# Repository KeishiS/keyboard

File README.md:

# README

## Dependencies

- `https://github.com/foostan/kbd`
- `https://github.com/keebio/Keebio-Parts.pretty`

```
> ln -s ./keyboard/keyboards/keishis $HOME/qmk_firmware/keyboards/keishis
> qmk compile -kb keishis/ot_board -km default
> qmk flash keishis_ot_board_default.hex
```

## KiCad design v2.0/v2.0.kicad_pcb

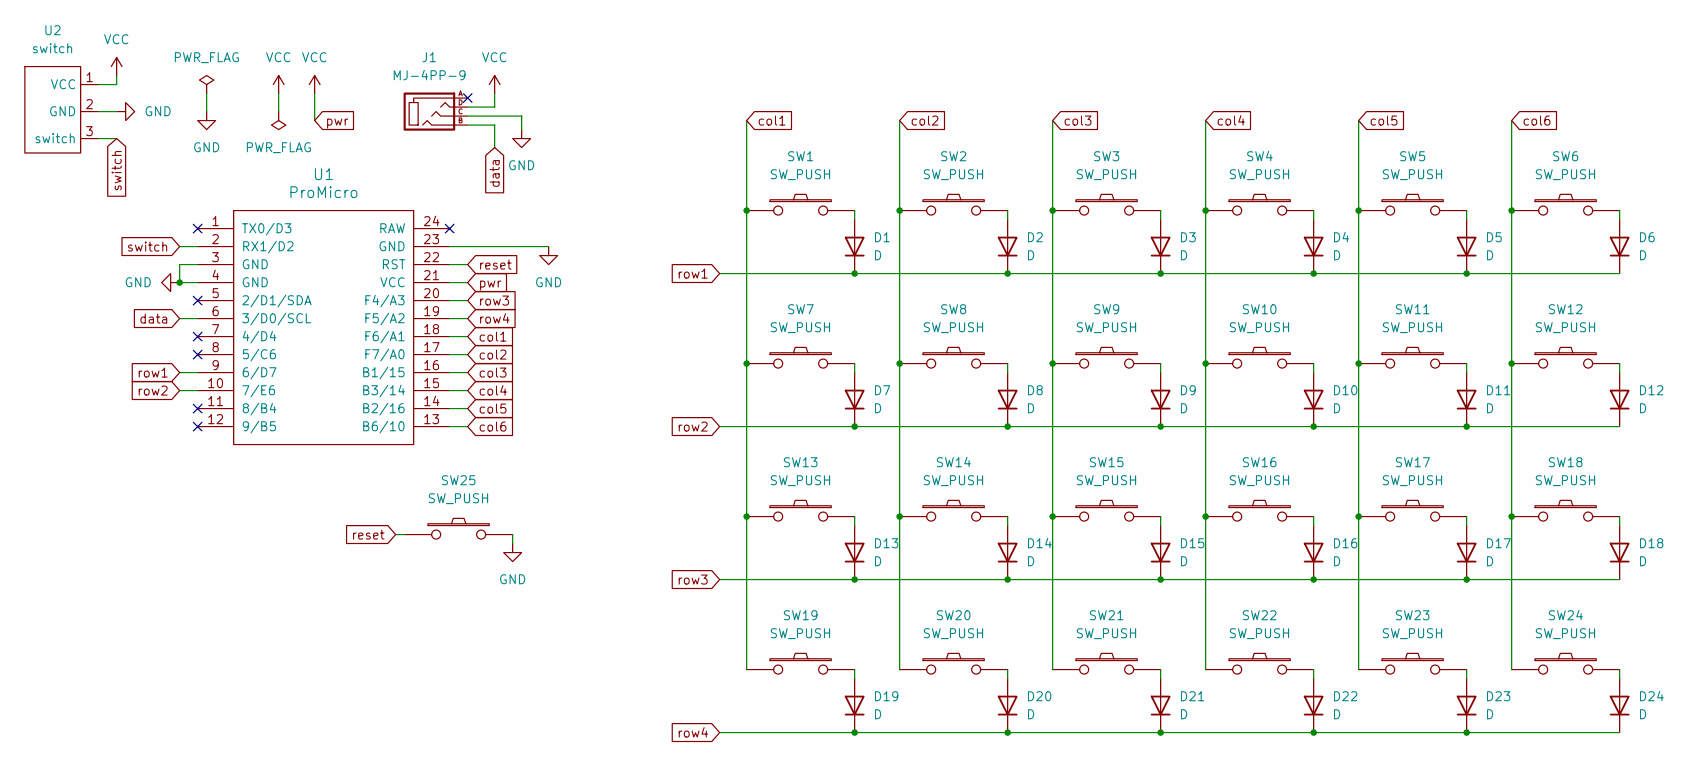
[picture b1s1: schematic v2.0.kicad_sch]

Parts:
D1, D2, D3, D4, D5, D6, D7, D8, D9, D10, D11, D12, D13, D14, D15, D16, D17, D18, D19, D20, D21, D22, D23, D24: D; Diode-dual
J1: MJ-4PP-9; MJ-4PP-9_reversible
SW1, SW2, SW3, SW4, SW5, SW6, SW7, SW8, SW9, SW10, SW11, SW12, SW13, SW14, SW15, SW16, SW17, SW18, SW19, SW20, SW21, SW22, SW23, SW24: SW_PUSH; choc1_0.8u_reversible
SW25: SW_PUSH; ResetSW
U1: ProMicro
U2: switch; triangle

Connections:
GND: J1.C, SW25.2, U1.3 (GND), U1.4 (GND), U1.23 (GND), U2.2 (GND)
unnamed: D1.2 (A), SW1.2
unnamed: D2.2 (A), SW2.2
unnamed: D3.2 (A), SW3.2
unnamed: D4.2 (A), SW4.2
unnamed: D5.2 (A), SW5.2
unnamed: D6.2 (A), SW6.2
unnamed: D7.2 (A), SW7.2
unnamed: D8.2 (A), SW8.2
unnamed: D9.2 (A), SW9.2
unnamed: D10.2 (A), SW10.2
unnamed: D11.2 (A), SW11.2
unnamed: D12.2 (A), SW12.2
unnamed: D13.2 (A), SW13.2
unnamed: D14.2 (A), SW14.2
unnamed: D15.2 (A), SW15.2
unnamed: D16.2 (A), SW16.2
unnamed: D17.2 (A), SW17.2
unnamed: D18.2 (A), SW18.2
unnamed: D19.2 (A), SW19.2
unnamed: D20.2 (A), SW20.2
unnamed: D21.2 (A), SW21.2
unnamed: D22.2 (A), SW22.2
unnamed: D23.2 (A), SW23.2
unnamed: D24.2 (A), SW24.2
col1: SW1.1, SW7.1, SW13.1, SW19.1, U1.18 (F6/A1)
col2: SW2.1, SW8.1, SW14.1, SW20.1, U1.17 (F7/A0)
col3: SW3.1, SW9.1, SW15.1, SW21.1, U1.16 (B1/15)
col4: SW4.1, SW10.1, SW16.1, SW22.1, U1.15 (B3/14)
col5: SW5.1, SW11.1, SW17.1, SW23.1, U1.14 (B2/16)
col6: SW6.1, SW12.1, SW18.1, SW24.1, U1.13 (B6/10)
data: J1.B, U1.6 (3/D0/SCL)
pwr: J1.D, U1.21 (VCC), U2.1 (VCC)
reset: SW25.1, U1.22 (RST)
row1: D1.1 (K), D2.1 (K), D3.1 (K), D4.1 (K), D5.1 (K), D6.1 (K), U1.9 (6/D7)
row2: D7.1 (K), D8.1 (K), D9.1 (K), D10.1 (K), D11.1 (K), D12.1 (K), U1.10 (7/E6)
row3: D13.1 (K), D14.1 (K), D15.1 (K), D16.1 (K), D17.1 (K), D18.1 (K), U1.20 (F4/A3)
row4: D19.1 (K), D20.1 (K), D21.1 (K), D22.1 (K), D23.1 (K), D24.1 (K), U1.19 (F5/A2)
switch: U1.2 (RX1/D2), U2.3 (switch)

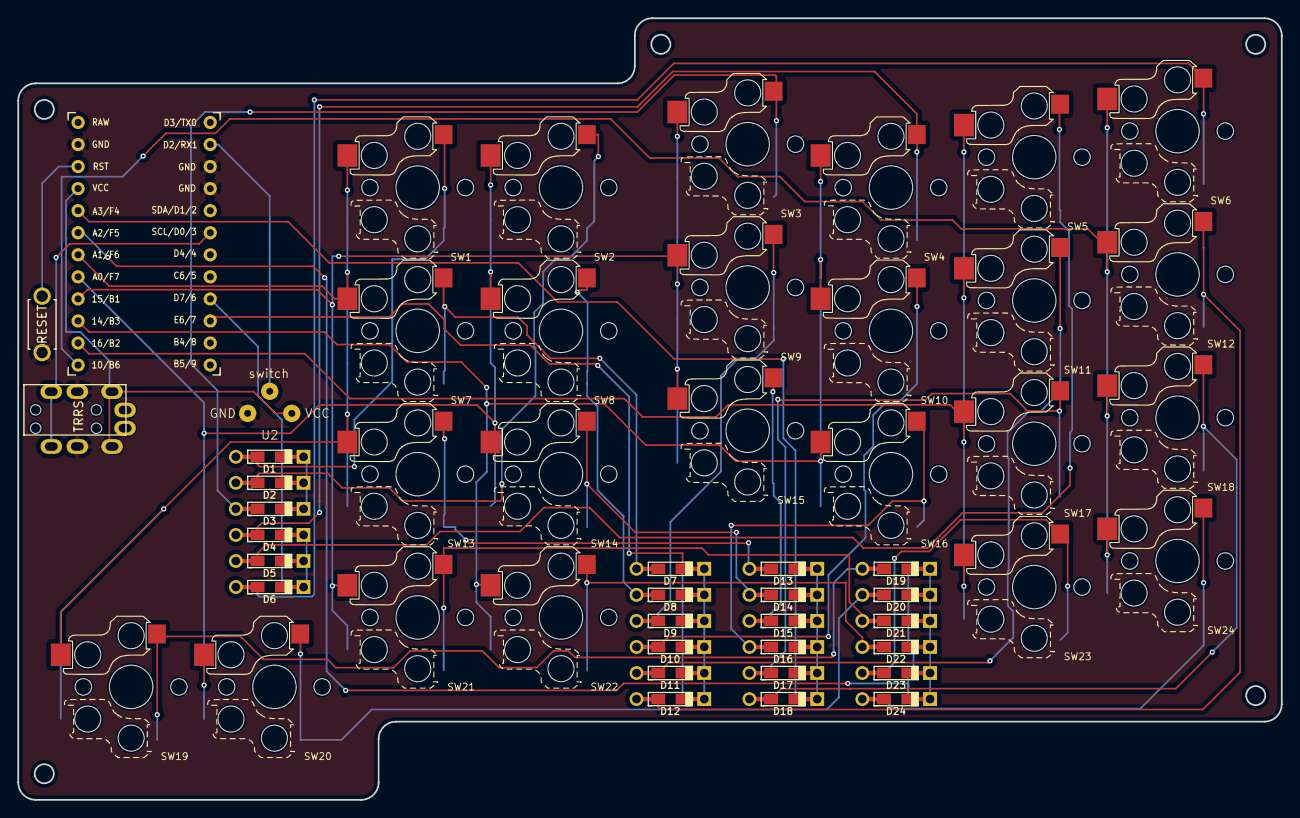
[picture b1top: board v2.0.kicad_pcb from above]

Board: 2 copper layers, 145.5 x 90.0 mm, 52 parts (0 on the bottom side), 39 nets.

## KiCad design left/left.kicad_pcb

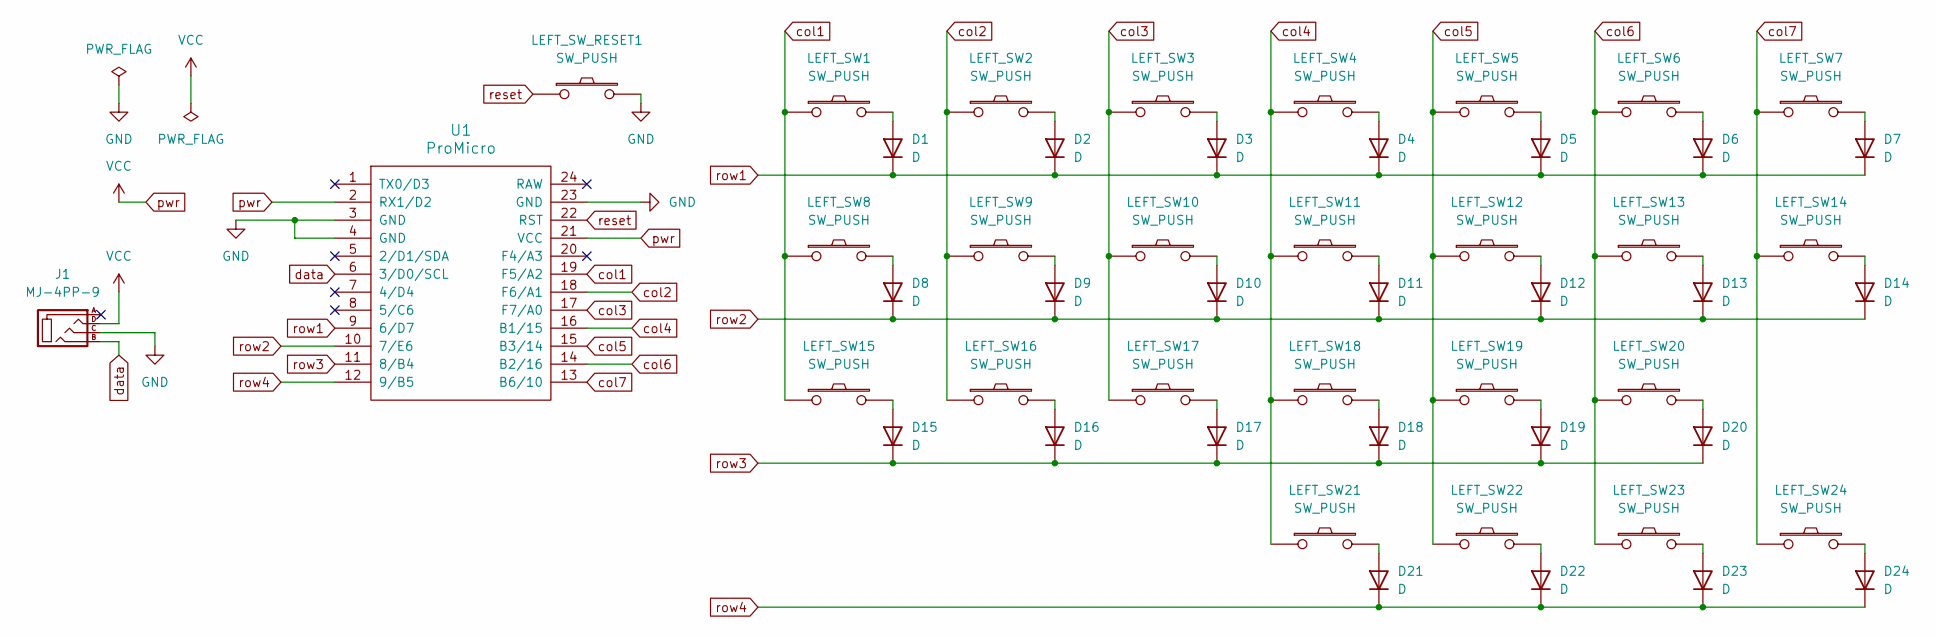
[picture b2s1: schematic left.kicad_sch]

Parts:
D1, D2, D3, D4, D5, D6, D7, D8, D9, D10, D11, D12, D13, D14, D15, D16, D17, D18, D19, D20, D21, D22, D23, D24: D; D3_TH_SMD
J1: MJ-4PP-9
LEFT_SW1, LEFT_SW2, LEFT_SW3, LEFT_SW4, LEFT_SW5, LEFT_SW6, LEFT_SW7, LEFT_SW8, LEFT_SW9, LEFT_SW10, LEFT_SW11, LEFT_SW12, LEFT_SW13, LEFT_SW14, LEFT_SW16, LEFT_SW17, LEFT_SW18, LEFT_SW19, LEFT_SW20, LEFT_SW21, LEFT_SW22, LEFT_SW23, LEFT_SW24: SW_PUSH; CherryMX_Choc_Hotswap
LEFT_SW15: SW_PUSH; CherryMX_Choc_Hotswap_1.5u
LEFT_SW_RESET1: SW_PUSH; ResetSW
U1: ProMicro; ProMicro_v2

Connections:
GND: J1.C, LEFT_SW_RESET1.2, U1.3 (GND), U1.4 (GND), U1.23 (GND)
unnamed: D1.2 (A), LEFT_SW1.2
unnamed: D2.2 (A), LEFT_SW2.2
unnamed: D3.2 (A), LEFT_SW3.2
unnamed: D4.2 (A), LEFT_SW4.2
unnamed: D5.2 (A), LEFT_SW5.2
unnamed: D6.2 (A), LEFT_SW6.2
unnamed: D7.2 (A), LEFT_SW7.2
unnamed: D8.2 (A), LEFT_SW8.2
unnamed: D9.2 (A), LEFT_SW9.2
unnamed: D10.2 (A), LEFT_SW10.2
unnamed: D11.2 (A), LEFT_SW11.2
unnamed: D12.2 (A), LEFT_SW12.2
unnamed: D13.2 (A), LEFT_SW13.2
unnamed: D14.2 (A), LEFT_SW14.2
unnamed: D15.2 (A), LEFT_SW15.2
unnamed: D16.2 (A), LEFT_SW16.2
unnamed: D17.2 (A), LEFT_SW17.2
unnamed: D18.2 (A), LEFT_SW18.2
unnamed: D19.2 (A), LEFT_SW19.2
unnamed: D20.2 (A), LEFT_SW20.2
unnamed: D21.2 (A), LEFT_SW21.2
unnamed: D22.2 (A), LEFT_SW22.2
unnamed: D23.2 (A), LEFT_SW23.2
unnamed: D24.2 (A), LEFT_SW24.2
col1: LEFT_SW1.1, LEFT_SW8.1, LEFT_SW15.1, U1.19 (F5/A2)
col2: LEFT_SW2.1, LEFT_SW9.1, LEFT_SW16.1, U1.18 (F6/A1)
col3: LEFT_SW3.1, LEFT_SW10.1, LEFT_SW17.1, U1.17 (F7/A0)
col4: LEFT_SW4.1, LEFT_SW11.1, LEFT_SW18.1, LEFT_SW21.1, U1.16 (B1/15)
col5: LEFT_SW5.1, LEFT_SW12.1, LEFT_SW19.1, LEFT_SW22.1, U1.15 (B3/14)
col6: LEFT_SW6.1, LEFT_SW13.1, LEFT_SW20.1, LEFT_SW23.1, U1.14 (B2/16)
col7: LEFT_SW7.1, LEFT_SW14.1, LEFT_SW24.1, U1.13 (B6/10)
data: J1.B, U1.6 (3/D0/SCL)
pwr: J1.D, U1.2 (RX1/D2), U1.21 (VCC)
reset: LEFT_SW_RESET1.1, U1.22 (RST)
row1: D1.1 (K), D2.1 (K), D3.1 (K), D4.1 (K), D5.1 (K), D6.1 (K), D7.1 (K), U1.9 (6/D7)
row2: D8.1 (K), D9.1 (K), D10.1 (K), D11.1 (K), D12.1 (K), D13.1 (K), D14.1 (K), U1.10 (7/E6)
row3: D15.1 (K), D16.1 (K), D17.1 (K), D18.1 (K), D19.1 (K), D20.1 (K), U1.11 (8/B4)
row4: D21.1 (K), D22.1 (K), D23.1 (K), D24.1 (K), U1.12 (9/B5)

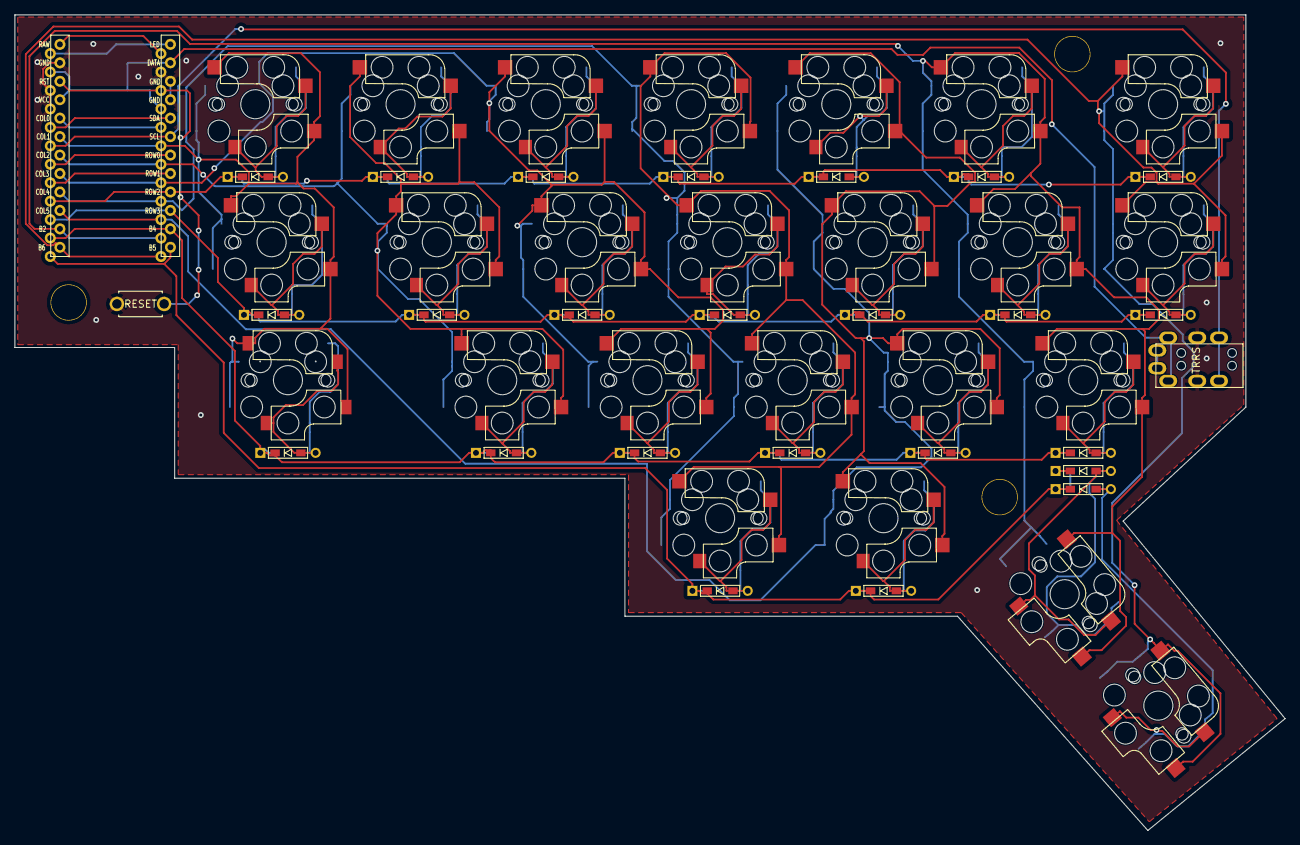
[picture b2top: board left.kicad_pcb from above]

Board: 2 copper layers, 174.9 x 112.3 mm, 54 parts (0 on the bottom side), 39 nets.

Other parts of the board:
Ref01: Val01; HOLE
Ref02: Val02; HOLE
Ref03: Val03; HOLE

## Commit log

2023-12-31 init
2023-12-31 updated PCB
2023-12-31 PCBの外枠追加
2023-12-31 外枠の微修正
2023-12-31 左手PCB完成
2024-01-01 配線まわりのファイル追加
2024-01-01 右手PCB作成
2024-01-03 左手PCBの組み換え．外枠は未完成
2024-01-03 左手PCBの発注済
2025-06-05 removed old one
2025-06-05 added new ver.
2025-06-24 done keymaping
2026-04-07 added a new keyboard
